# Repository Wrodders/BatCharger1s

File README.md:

# BatCharger1s
USBC-PD 1S LiPo/Ion Battery Charger

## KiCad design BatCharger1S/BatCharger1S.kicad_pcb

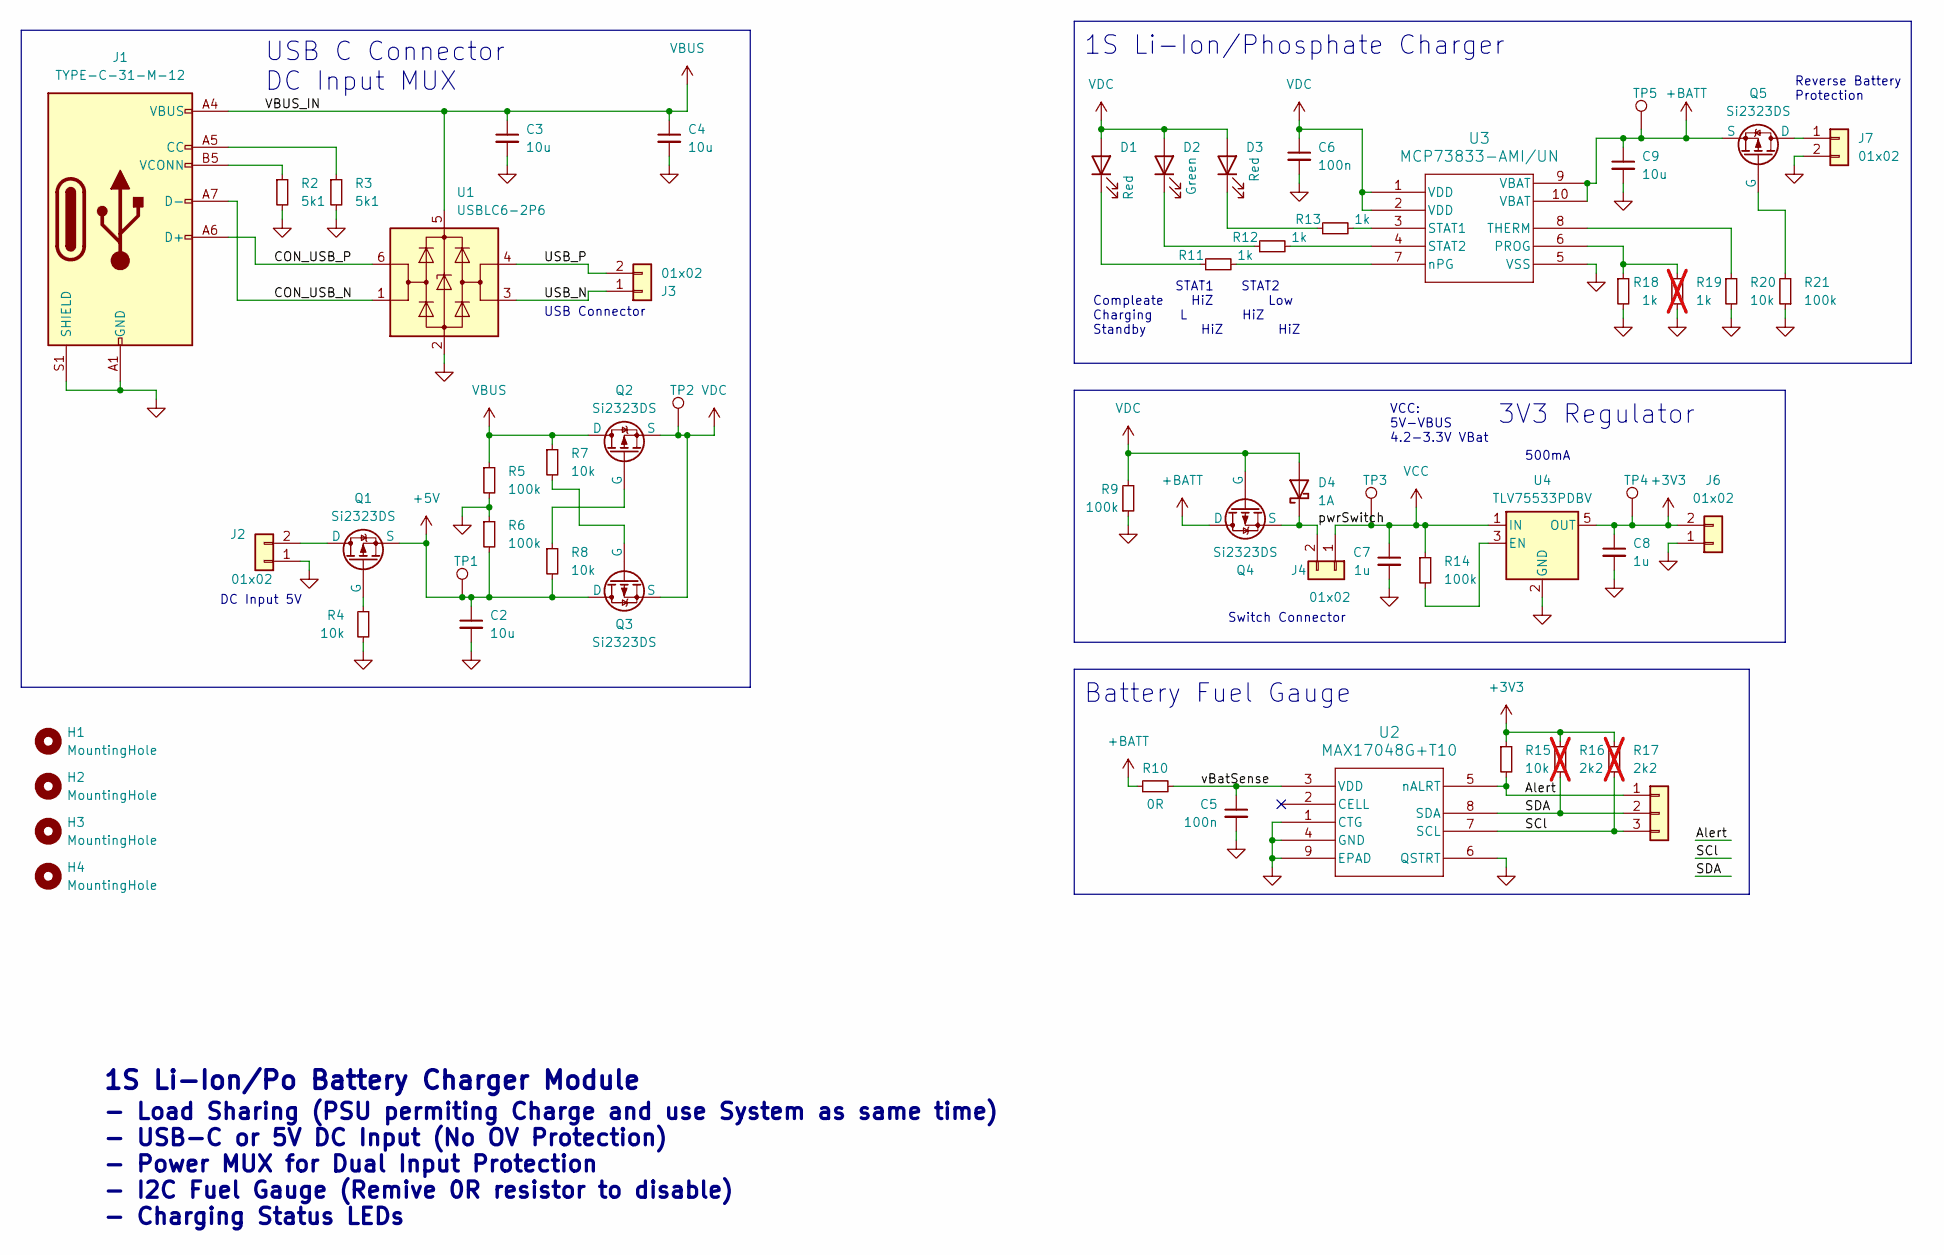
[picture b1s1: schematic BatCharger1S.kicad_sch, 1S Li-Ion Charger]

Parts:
C2: 10u; C_0805_2012Metric_Pad1.18x1.45mm_HandSolder
C3, C4, C9: 10u; C_0603_1608Metric_Pad1.08x0.95mm_HandSolder
C5, C6: 100n; C_0603_1608Metric_Pad1.08x0.95mm_HandSolder
C7, C8: 1u; C_0603_1608Metric_Pad1.08x0.95mm_HandSolder
D1, D3: Red; LED_0201_0603Metric_Pad0.64x0.40mm_HandSolder
D2: Green; LED_0201_0603Metric_Pad0.64x0.40mm_HandSolder
D4: 1A; D_1206_3216Metric_Pad1.42x1.75mm_HandSolder
H1, H2, H3, H4: MountingHole; MountingHole_2.2mm_M2
J1: TYPE-C-31-M-12
J2, J3, J6, J7: 01x02; JST_EH_B2B-EH-A_1x02_P2.50mm_Vertical
J4: 01x02; PinHeader_1x02_P2.54mm_Vertical
J5: Conn_01x03; JST_EH_B3B-EH-A_1x03_P2.50mm_Vertical
Q1, Q2, Q3, Q4, Q5: Si2323DS; SOT-23-3
R2, R3: 5k1; R_0603_1608Metric_Pad0.98x0.95mm_HandSolder
R4, R7, R8, R15, R20: 10k; R_0603_1608Metric_Pad0.98x0.95mm_HandSolder
R5, R6, R9, R14, R21: 100k; R_0603_1608Metric_Pad0.98x0.95mm_HandSolder
R10: 0R; R_0603_1608Metric_Pad0.98x0.95mm_HandSolder
R11, R12, R13, R18: 1k; R_0603_1608Metric_Pad0.98x0.95mm_HandSolder
R16, R17: 2k2; R_0603_1608Metric_Pad0.98x0.95mm_HandSolder; not fitted
R19: 1k; R_0603_1608Metric_Pad0.98x0.95mm_HandSolder; not fitted
TP1, TP2, TP3, TP4, TP5: TestPoint; TestPoint_Pad_D1.0mm
U1: USBLC6-2P6; SOT-666
U2: MAX17048G+T10; TDFN-8-1EP_2x2mm_P0.5mm_EP0.8x1.2mm
U3: MCP73833-AMI/UN; MSOP-10_3x3mm_P0.5mm
U4: TLV75533PDBV; SOT-23-5

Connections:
+3V3: C8.1, J6.2, R15.1, R16.1, R17.1, TP4.1, U4.5 (OUT)
+5V: C2.1, Q1.3 (S), Q3.1 (D), R6.2, R8.2, TP1.1
+BATT: C9.1, Q4.1 (D), Q5.3 (S), R10.1, TP5.1, U3.9 (VBAT), U3.10 (VBAT)
/Alert: J5.1, R15.2, U2.5 (nALRT)
/CON_USB_N: J1.A7 (D-), U1.1 (I/O1)
/CON_USB_P: J1.A6 (D+), U1.6 (I/O1)
/SCl: J5.3, R17.2, U2.7 (SCL)
/SDA: J5.2, R16.2, U2.8 (SDA)
/USB_N: J3.1, U1.3 (I/O2)
/USB_P: J3.2, U1.4 (I/O2)
/pwrSwitch: D4.1 (K), J4.2, Q4.3 (S)
/vBatSense: C5.1, R10.2, U2.3 (VDD)
GND: C2.2, C3.2, C4.2, C5.2, C6.2, C7.2, C8.2, C9.2, J1.A1 (GND), J1.A12 (GND), J1.B1 (GND), J1.B12 (GND), J1.S1 (SHIELD), J2.1, J6.1, J7.2, R2.2, R3.2, R4.2, R5.2, R6.1, R9.1, R18.2, R19.2, R20.2, R21.1, U1.2 (GND), U2.1 (CTG), U2.4 (GND), U2.6 (QSTRT), U2.9 (EPAD), U3.5 (VSS), U4.2 (GND)
unnamed: D1.1 (K), R11.1
unnamed: D2.1 (K), R12.1
unnamed: D3.1 (K), R13.1
unnamed: J1.A5 (CC), R3.1
unnamed: J1.B5 (VCONN), R2.1
unnamed: J2.2, Q1.1 (D)
unnamed: J7.1, Q5.1 (D)
unnamed: Q1.2 (G), R4.1
unnamed: Q2.2 (G), R8.1
unnamed: Q3.2 (G), R7.2
unnamed: Q5.2 (G), R21.2
unnamed: R18.1, R19.1, U3.6 (PROG)
unnamed: R13.2, U3.3 (STAT1)
unnamed: R12.2, U3.4 (STAT2)
unnamed: R20.1, U3.8 (THERM)
unnamed: R11.2, U3.7 (nPG)
unnamed: R14.2, U4.3 (EN)
VBUS: C3.1, C4.1, J1.A4 (VBUS), J1.A9 (VBUS), J1.B4 (VBUS), J1.B9 (VBUS), Q2.1 (D), R5.1, R7.1, U1.5 (VBUS)
VCC: C7.1, J4.1, R14.1, TP3.1, U4.1 (IN)
VDC: C6.1, D1.2 (A), D2.2 (A), D3.2 (A), D4.2 (A), Q2.3 (S), Q3.3 (S), Q4.2 (G), R9.2, TP2.1, U3.1 (VDD), U3.2 (VDD)

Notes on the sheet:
Switch Connector
USB Connector
500mA
Reverse Battery Protection
3V3 Regulator
1S Li-Ion/Po Battery Charger Module
DC Input 5V
VCC: 5V-VBUS 4.2-3.3V VBat
USB C Connector DC Input MUX
1S Li-Ion/Phosphate Charger
- Load Sharing (PSU permiting Charge and use System as same time) - USB-C or 5V DC Input (No OV Protection) - Power MUX for Dual Input Protection - I2C Fuel Gauge (Remive 0R resistor to disable) - Charging Status LEDs
Battery Fuel Gauge
STAT1 STAT2 Compleate HiZ Low Charging L HiZ Standby HiZ HiZ

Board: 2 copper layers, 57 parts (0 on the bottom side), 33 nets, no tracks yet.

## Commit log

2023-11-23 v0.1
2023-11-23 footprintAssigment
2023-11-27 PCBv0.1
2023-12-03 v2Layout
